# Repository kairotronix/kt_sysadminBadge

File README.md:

# SysAdmin Badge

This is the PCB design for the SysAdmin Day badge.

The badge design is inspired by deep thought, from The Hitchhiker's Guide to the Galaxy.

The LCD being used is a standard 1.3" 240x240 display from Ali Express. Searching `1.3 inch IPS display TFT LCD 1.3" Display Screen Module 240*240 ST7789 Drive IC SPI HD Full Color for IPS Display Module 240X240` and selecting the "welded" or "soldered" variety will yield the correct board. 

The soldered-on cable was chosen for cost reduction.

# What is the idea
In case of fire, a quick reaction is needed, but if you just woke up, if you are in the bathroom or in any compromising situation, the sysadmin must always respond to the user, and then fix the incident.

For this reason, we have designed a random excuse generator that will give you a perfect SLA, even in desperate moments.

Note: Answers may be satirical, so use at your own risk. 

## History
The System Administrator Appreciation Day, It is celebrated on the last Friday of July since the year 2000.

The holiday was started by a system administrator nicknamed Sleeping Beauty (AS). He got his inspiration from a Hewlett-Packard magazine ad, in which an administrator's co-workers gave him flowers and a fruit basket for setting up their new printers and a pillow to rest on in their spare time.

Wait… what exactly is SysAdmin Day? it’s only the single greatest 24 hours on the planet… and pretty much the most important holiday of the year. It’s also the perfect opportunity to pay tribute to the heroic men and women who, come rain or shine, prevent disasters, keep IT secure and put out tech fires left and right.

At this point, you may be thinking, “Great. I get it. My SysAdmin is a rock star. But now what?” Glad you asked! Proper observation of SysAdmin Day includes (but is not limited to):

Cake & Ice cream

Pizza

Cards

Gifts

Words of gratitude

Custom t-shirts celebrating the epic greatness of your SysAdmin

Balloons

Confetti

Did I say gifts

# Conclusion
Why make one badge electronic? Because is one good gift of your SysAdmin.

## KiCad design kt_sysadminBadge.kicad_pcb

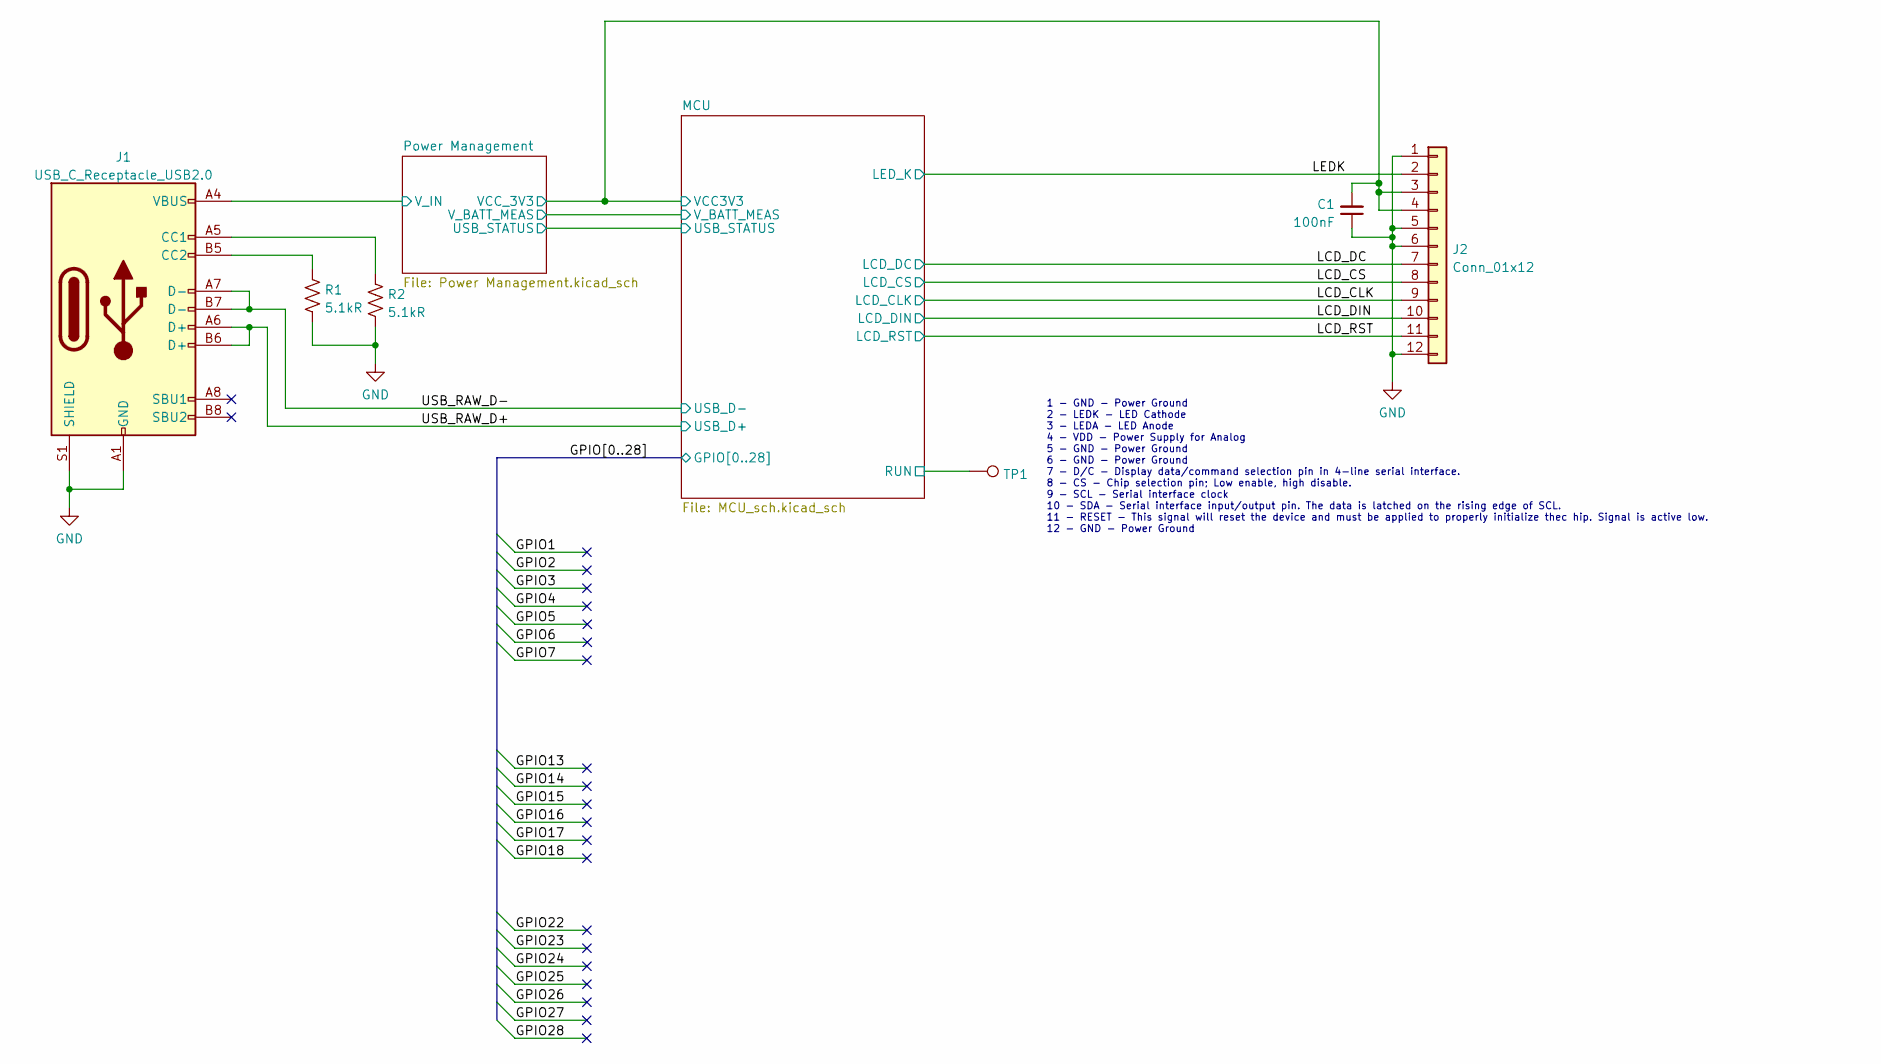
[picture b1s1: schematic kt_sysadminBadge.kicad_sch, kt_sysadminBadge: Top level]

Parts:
C1: 100nF; C_0603_1608Metric_Pad1.08x0.95mm_HandSolder; MFG P/N CL10B104KB8NNNC; LCSC P/N C1591
J1: USB_C_Receptacle_USB2.0; USB_C_Receptacle_XKB_U262-16XN-4BVC11; MFG P/N U262-161N-4BVC11; LCSC P/N C319148
J2: Conn_01x12; st7789-240-240
R1, R2: 5.1kR; R_0603_1608Metric_Pad0.98x0.95mm_HandSolder
TP1: TestPoint; TestPoint_Pad_D1.0mm

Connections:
/LCD_CLK: J2.9; also elsewhere on the board
/LCD_CS: J2.8; also elsewhere on the board
/LCD_DC: J2.7; also elsewhere on the board
/LCD_DIN: J2.10; also elsewhere on the board
/LCD_RST: J2.11; also elsewhere on the board
/LEDK: J2.2; also elsewhere on the board
/MCU/RUN: TP1.1; also elsewhere on the board
/MCU/VCC3V3: C1.2, J2.3, J2.4; also elsewhere on the board
/Power Management/V_USB: J1.A4 (VBUS), J1.A9 (VBUS), J1.B4 (VBUS), J1.B9 (VBUS); also elsewhere on the board
/USB_RAW_D+: J1.A6 (D+), J1.B6 (D+); also elsewhere on the board
/USB_RAW_D-: J1.A7 (D-), J1.B7 (D-); also elsewhere on the board
GND: C1.1, J1.A1 (GND), J1.A12 (GND), J1.B1 (GND), J1.B12 (GND), J1.S1 (SHIELD), J2.1, J2.5, J2.6, J2.12, R1.2, R2.2; also elsewhere on the board
unnamed: J1.A5 (CC1), R2.1
unnamed: J1.B5 (CC2), R1.1

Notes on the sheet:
1 - GND - Power Ground 2 - LEDK - LED Cathode 3 - LEDA - LED Anode 4 - VDD - Power Supply for Analog 5 - GND - Power Ground 6 - GND - Power Ground 7 - D/C - Display data/command selection pin in 4-line serial interface. 8 - CS - Chip selection pin; Low enable, high disable. 9 - SCL - Serial interfa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

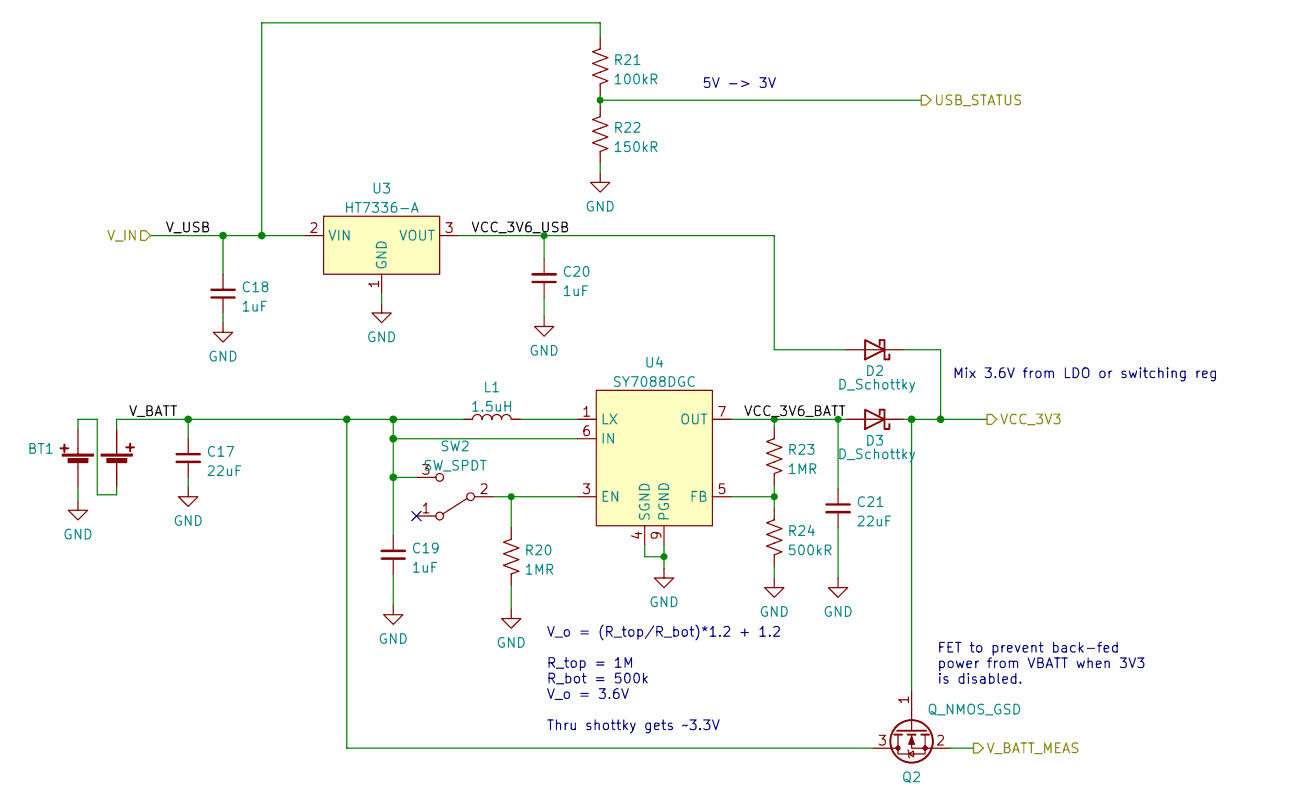
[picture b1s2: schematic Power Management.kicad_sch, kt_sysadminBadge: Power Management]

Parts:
BT1: MFG P/N BH-AAA-B5AA001; LCSC P/N C964881
C17, C21: 22uF; C_0805_2012Metric_Pad1.18x1.45mm_HandSolder; MFG P/N CL21A226MAYNNNE; LCSC P/N C602037
C18, C19, C20: 1uF; C_0603_1608Metric_Pad1.08x0.95mm_HandSolder; MFG P/N CL10A105KO8NNNC; LCSC P/N C1592
D2, D3: D_Schottky; D_SMA_Handsoldering; MFG P/N SS24; LCSC P/N C266555
L1: 1.5uH; L_1008_2520Metric_Pad1.43x2.20mm_HandSolder; MFG P/N HEI252012A-1R5M-Q8; LCSC P/N C285916
Q2: Q_NMOS_GSD; SC-59_Handsoldering; MFG P/N AP2302B; LCSC P/N C406812
R20, R23: 1MR; R_0603_1608Metric_Pad0.98x0.95mm_HandSolder; MFG P/N ARG03BTC1004; LCSC P/N C319876
R21: 100kR; R_0603_1608Metric_Pad0.98x0.95mm_HandSolder; MFG P/N AR03BTCX1003; LCSC P/N C335092
R22: 150kR; R_0603_1608Metric_Pad0.98x0.95mm_HandSolder; MFG P/N AR03BTCX1503; LCSC P/N C319969
R24: 500kR; R_0603_1608Metric_Pad0.98x0.95mm_HandSolder; MFG P/N AR03BTC5003N; LCSC P/N C412382
SW2: SW_SPDT; SW_SPDT_PCM12; MFG P/N K3-1296S-E2; LCSC P/N C136659
U3: HT7336-A; SOT-89-3_Handsoldering; MFG P/N HT7336-A; LCSC P/N C347192
U4: SY7088DGC; DFN-8-1EP_3x2mm_P0.5mm_EP1.7x1.4mm; MFG P/N SY7088DGC; LCSC P/N C178240

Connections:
/MCU/USB_STATUS: R21.2, R22.1; also elsewhere on the board
/MCU/VCC3V3: D2.1 (K), D3.1 (K), Q2.1 (G); also elsewhere on the board
/MCU/V_BATT_MEAS: Q2.2 (S); also elsewhere on the board
/Power Management/VCC_3V6_BATT: C21.1, D3.2 (A), R23.1, U4.7 (OUT), U4.8 (OUT)
/Power Management/VCC_3V6_USB: C20.2, D2.2 (A), U3.3 (VOUT)
/Power Management/V_BATT: BT1.2 (+), C17.1, C19.2, L1.1, Q2.3 (D), SW2.3 (C), U4.6 (IN)
/Power Management/V_USB: C18.2, R21.1, U3.2 (VIN); also elsewhere on the board
GND: BT1.3 (-), C17.2, C18.1, C19.1, C20.1, C21.2, R20.2, R22.2, R24.2, U3.1 (GND), U4.4 (SGND), U4.9 (PGND); also elsewhere on the board
unnamed: BT1.1 (-), BT1.4 (+)
unnamed: L1.2, U4.1 (LX), U4.2 (LX)
unnamed: R20.1, SW2.2 (B), U4.3 (EN)
unnamed: R23.2, R24.1, U4.5 (FB)

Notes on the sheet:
V_o = (R_top/R_bot)*1.2 + 1.2 R_top = 1M R_bot = 500k V_o = 3.6V Thru shottky gets ~3.3V
Mix 3.6V from LDO or switching reg
5V -> 3V
FET to prevent back-fed power from VBATT when 3V3 is disabled.

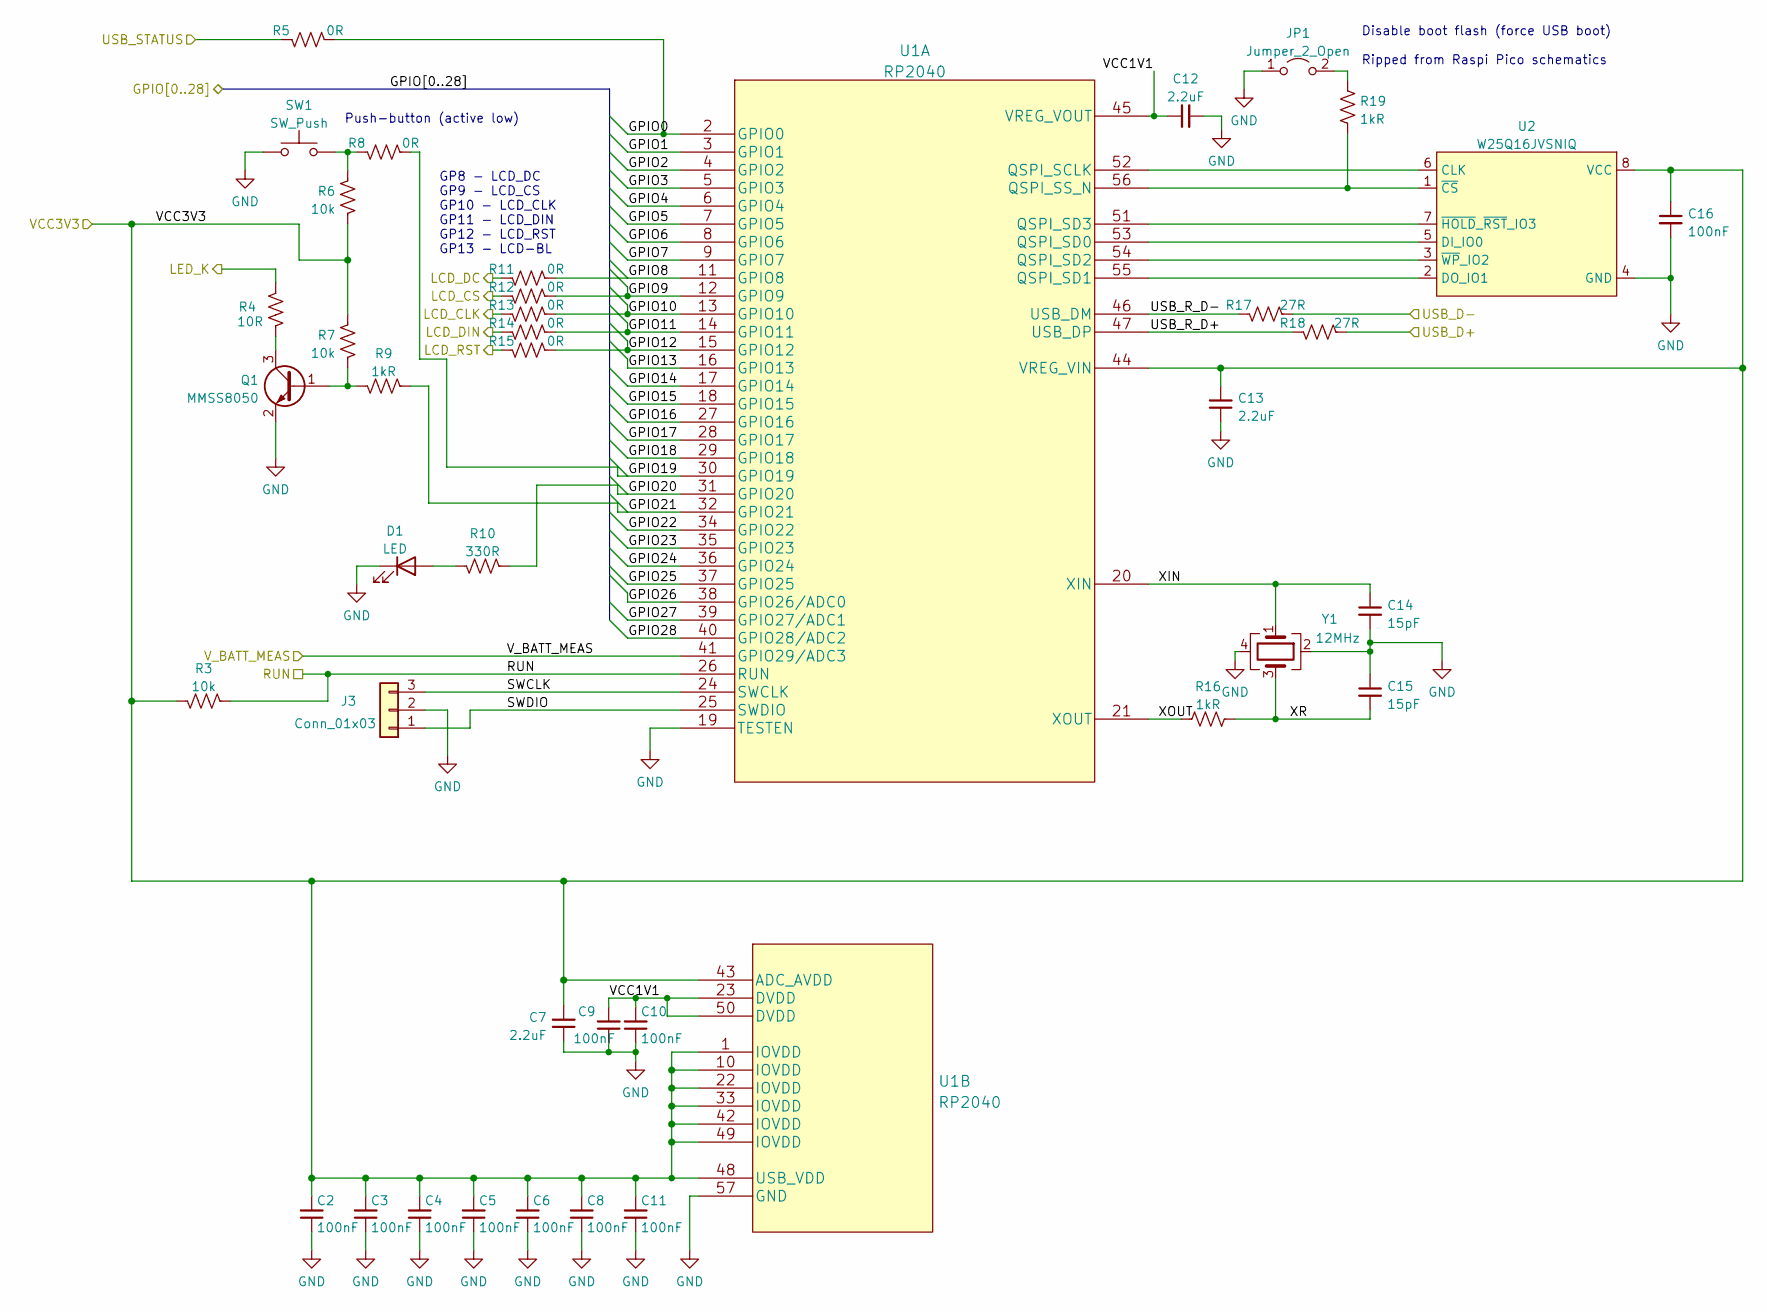
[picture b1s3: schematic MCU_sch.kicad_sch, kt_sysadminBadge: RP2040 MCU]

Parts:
C2, C3, C4, C5, C6, C8, C9, C10, C11, C16: 100nF; C_0603_1608Metric_Pad1.08x0.95mm_HandSolder; MFG P/N CL10B104KB8NNNC; LCSC P/N C1591
C7, C12, C13: 2.2uF; C_0603_1608Metric_Pad1.08x0.95mm_HandSolder; MFG P/N CL10A225KO8NNNC; LCSC P/N C23630
C14, C15: 15pF; C_0603_1608Metric_Pad1.08x0.95mm_HandSolder; MFG P/N CC0603JRNPO9BN150; LCSC P/N C107037
D1: LED; LED_D3.0mm; MFG P/N 204-10SURD/S530-A3-L; LCSC P/N C99771
J3: Conn_01x03; PinHeader_1x03_P2.54mm_Vertical
JP1: Jumper_2_Open; SolderJumper-2_P1.3mm_Open_TrianglePad1.0x1.5mm
Q1: MMSS8050; SC-59_Handsoldering; MFG P/N MMSS8050-H-TP; LCSC P/N C90158
R3, R6, R7: 10k; R_0603_1608Metric_Pad0.98x0.95mm_HandSolder; MFG P/N ARG03BTC1002; LCSC P/N C98220
R4: 10R; R_0603_1608Metric_Pad0.98x0.95mm_HandSolder; MFG P/N ERJUP3J100V; LCSC P/N C309083
R5, R8, R11, R12, R13, R14, R15: 0R; R_0603_1608Metric_Pad0.98x0.95mm_HandSolder; MFG P/N RC0603FR-0710KL; LCSC P/N C491193
R9, R16, R19: 1kR; R_0603_1608Metric_Pad0.98x0.95mm_HandSolder; MFG P/N ERJPB3B1001V; LCSC P/N C193680
R10: 330R; R_0603_1608Metric_Pad0.98x0.95mm_HandSolder; MFG P/N ERJ3RBD3300V; LCSC P/N C416699
R17, R18: 27R; R_0603_1608Metric_Pad0.98x0.95mm_HandSolder; MFG P/N ERJ3GEYJ270V; LCSC P/N C403464
SW1: SW_Push; SW_Push_1P1T_NO_6x6mm_H9.5mm; MFG P/N TSA063G50-250; LCSC P/N C294565
U1: RP2040; IC57_RP2040; MFG P/N RP2040; LCSC P/N C2040
U2: W25Q16JVSNIQ; SOIC-8_3.9x4.9mm_P1.27mm; MFG P/N W25Q16JVSNIQ; LCSC P/N C115407
Y1: 12MHz; Crystal_SMD_3225-4Pin_3.2x2.5mm_HandSoldering; MFG P/N 3TJ412000UYFBC; LCSC P/N C2681245

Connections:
/GPIO0: R5.1, U1.2 (GPIO0); also elsewhere on the board
/GPIO8: R11.1, U1.11 (GPIO8); also elsewhere on the board
/GPIO9: R12.1, U1.12 (GPIO9); also elsewhere on the board
/GPIO10: R13.1, U1.13 (GPIO10); also elsewhere on the board
/GPIO11: R14.1, U1.14 (GPIO11); also elsewhere on the board
/GPIO12: R15.1, U1.15 (GPIO12); also elsewhere on the board
/GPIO19: R8.1, U1.30 (GPIO19); also elsewhere on the board
/GPIO20: R10.1, U1.31 (GPIO20); also elsewhere on the board
/GPIO21: R9.1, U1.32 (GPIO21); also elsewhere on the board
/LCD_CLK: R13.2; also elsewhere on the board
/LCD_CS: R12.2; also elsewhere on the board
/LCD_DC: R11.2; also elsewhere on the board
/LCD_DIN: R14.2; also elsewhere on the board
/LCD_RST: R15.2; also elsewhere on the board
/LEDK: R4.1; also elsewhere on the board
/MCU/RUN: R3.2, U1.26 (RUN); also elsewhere on the board
/MCU/SWCLK: J3.3, U1.24 (SWCLK); also elsewhere on the board
/MCU/SWDIO: J3.1, U1.25 (SWDIO); also elsewhere on the board
/MCU/USB_R_D+: R18.2, U1.47 (USB_DP); also elsewhere on the board
/MCU/USB_R_D-: R17.2, U1.46 (USB_DM); also elsewhere on the board
/MCU/USB_STATUS: R5.2; also elsewhere on the board
/MCU/VCC1V1: C9.2, C10.2, C12.1, U1.23 (DVDD), U1.45 (VREG_VOUT), U1.50 (DVDD); also elsewhere on the board
/MCU/VCC3V3: C2.2, C3.2, C4.2, C5.2, C6.2, C7.2, C8.2, C11.2, C13.2, C16.1, R3.1, R6.2, R7.1, U1.1 (IOVDD), U1.10 (IOVDD), U1.22 (IOVDD), U1.33 (IOVDD), U1.42 (IOVDD), U1.43 (ADC_AVDD), U1.44 (VREG_VIN), U1.48 (USB_VDD), U1.49 (IOVDD), U2.8 (VCC); also elsewhere on the board
/MCU/XIN: C14.1, U1.20 (XIN), Y1.1; also elsewhere on the board
/MCU/XOUT: R16.2, U1.21 (XOUT); also elsewhere on the board
/MCU/XR: C15.2, R16.1, Y1.3
/USB_RAW_D+: R18.1; also elsewhere on the board
/USB_RAW_D-: R17.1; also elsewhere on the board
GND: C2.1, C3.1, C4.1, C5.1, C6.1, C7.1, C8.1, C9.1, C10.1, C11.1, C12.2, C13.1, C14.2, C15.1, C16.2, D1.1 (K), J3.2, JP1.1 (A), Q1.2 (E), SW1.2, U1.19 (TESTEN), U1.57 (GND), U2.4 (GND), Y1.2, Y1.4; also elsewhere on the board
unnamed: D1.2 (A), R10.2
unnamed: JP1.2 (B), R19.1
unnamed: Q1.1 (B), R7.2, R9.2
unnamed: Q1.3 (C), R4.2
unnamed: R6.1, R8.2, SW1.1
unnamed 63: R19.2, U1.56 (QSPI_SS_N), U2.1 (~CS); also elsewhere on the board
unnamed 66: U1.51 (QSPI_SD3), U2.7 (~HOLD_~RST_IO3); also elsewhere on the board
unnamed 67: U1.52 (QSPI_SCLK), U2.6 (CLK); also elsewhere on the board
unnamed 68: U1.53 (QSPI_SD0), U2.5 (DI_IO0); also elsewhere on the board
unnamed 69: U1.54 (QSPI_SD2), U2.3 (~WP_IO2); also elsewhere on the board
unnamed 70: U1.55 (QSPI_SD1), U2.2 (DO_IO1); also elsewhere on the board

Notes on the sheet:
Disable boot flash (force USB boot) Ripped from Raspi Pico schematics
Push-button (active low)
GP8 - LCD_DC GP9 - LCD_CS GP10 - LCD_CLK GP11 - LCD_DIN GP12 - LCD_RST GP13 - LCD-BL

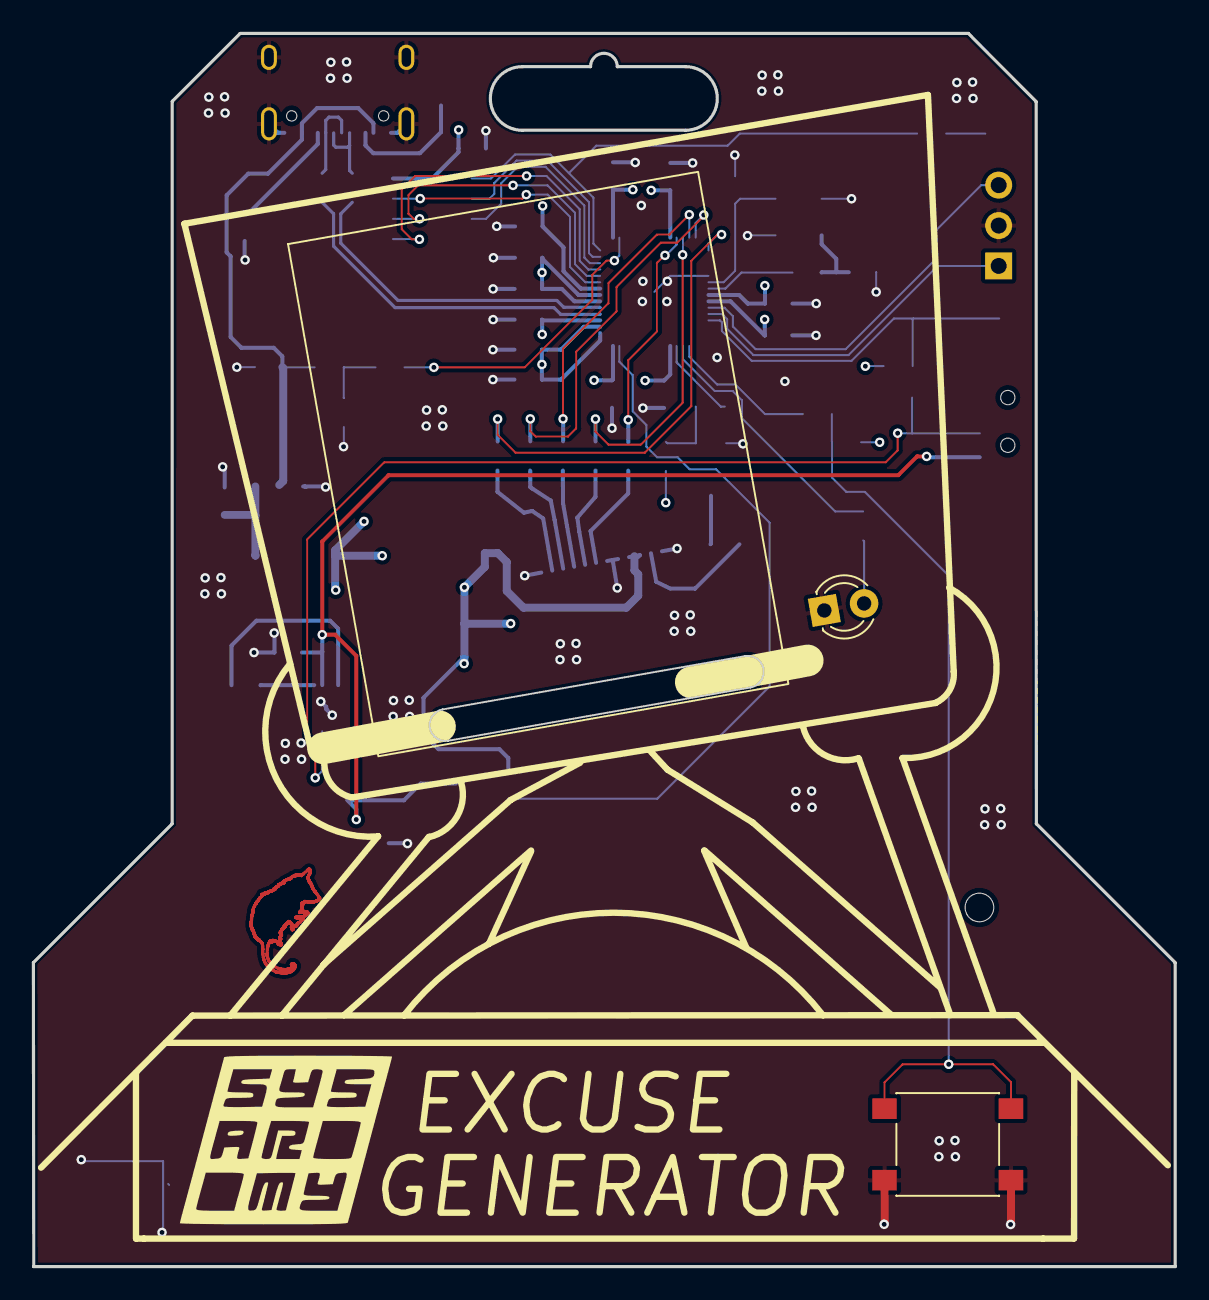
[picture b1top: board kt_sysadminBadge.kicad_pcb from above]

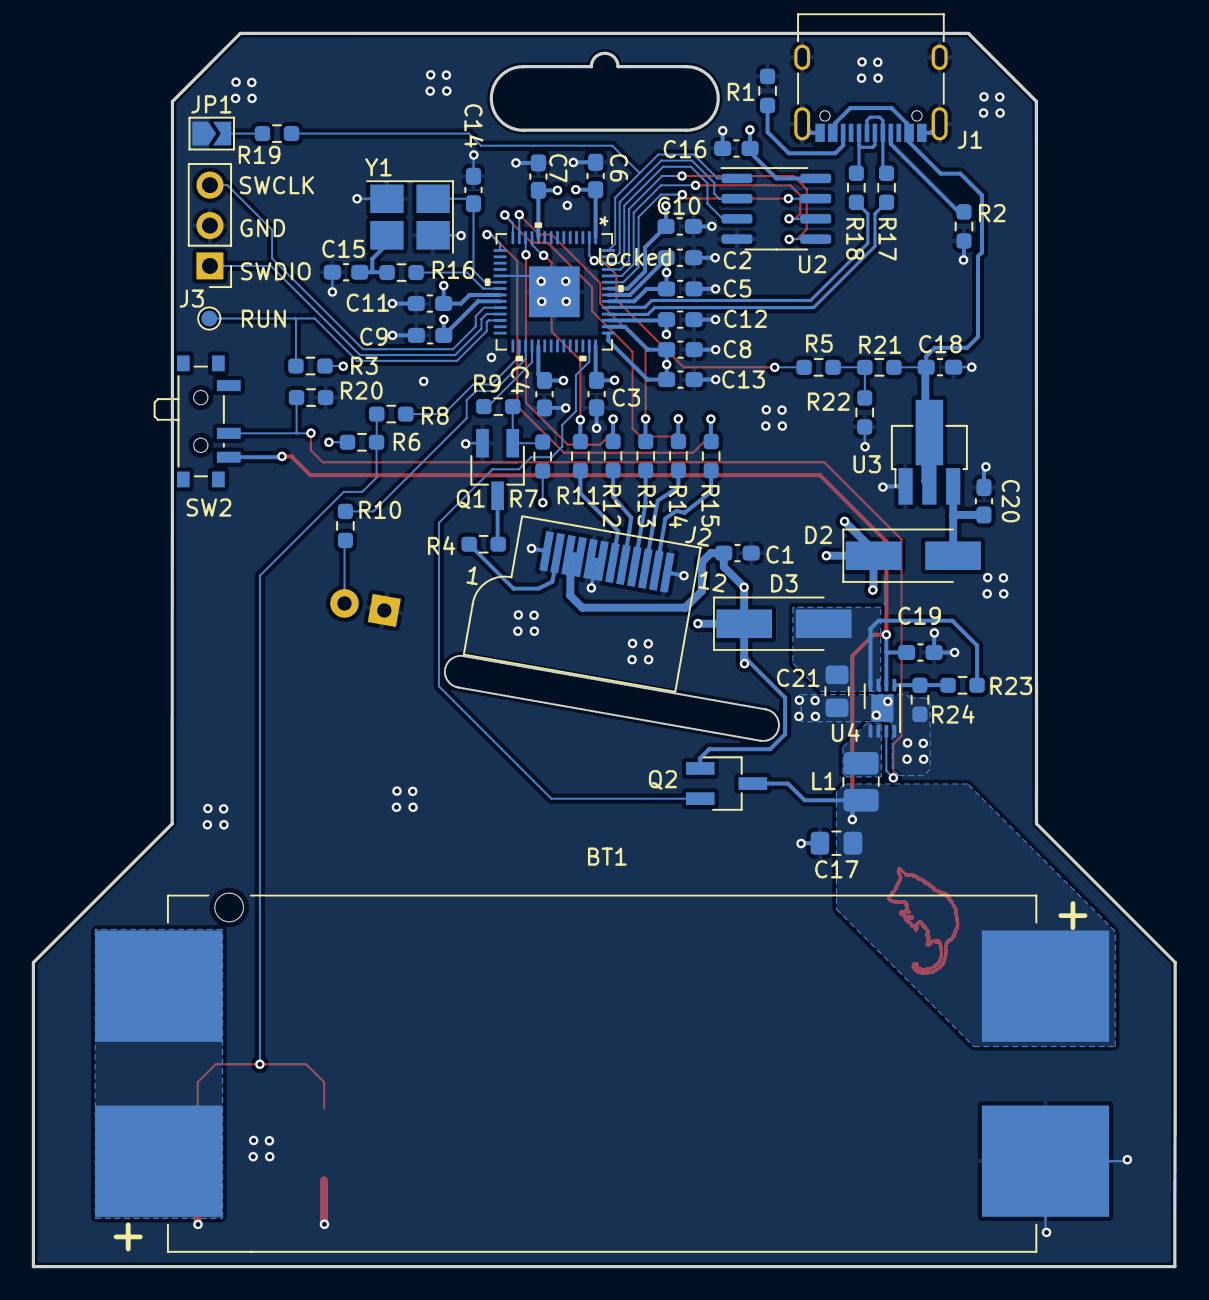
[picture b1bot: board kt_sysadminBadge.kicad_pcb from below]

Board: 4 copper layers, 71.8 x 77.5 mm, 64 parts (61 on the bottom side), 51 nets.

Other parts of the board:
locked: locked; IC57_RP2040

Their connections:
/GPIO0: locked.2 (GPIO0); also elsewhere on the board
/GPIO8: locked.11 (GPIO8); also elsewhere on the board
/GPIO9: locked.12 (GPIO9); also elsewhere on the board
/GPIO10: locked.13 (GPIO10); also elsewhere on the board
/GPIO11: locked.14 (GPIO11); also elsewhere on the board
/GPIO12: locked.15 (GPIO12); also elsewhere on the board
/GPIO19: locked.30 (GPIO19); also elsewhere on the board
/GPIO20: locked.31 (GPIO20); also elsewhere on the board
/GPIO21: locked.32 (GPIO21); also elsewhere on the board
/MCU/RUN: locked.26 (RUN); also elsewhere on the board
/MCU/SWCLK: locked.24 (SWCLK); also elsewhere on the board
/MCU/SWDIO: locked.25 (SWDIO); also elsewhere on the board
/MCU/USB_R_D+: locked.47 (USB_DP); also elsewhere on the board
/MCU/USB_R_D-: locked.46 (USB_DM); also elsewhere on the board
/MCU/VCC1V1: locked.23 (DVDD), locked.45 (VREG_VOUT), locked.50 (DVDD); also elsewhere on the board
/MCU/VCC3V3: locked.1 (IOVDD), locked.10 (IOVDD), locked.22 (IOVDD), locked.33 (IOVDD), locked.42 (IOVDD), locked.43 (ADC_AVDD), locked.44 (VREG_VIN), locked.48 (USB_VDD), locked.49 (IOVDD); also elsewhere on the board
/MCU/V_BATT_MEAS: locked.41 (GPIO29/ADC3); also elsewhere on the board
/MCU/XIN: locked.20 (XIN); also elsewhere on the board
/MCU/XOUT: locked.21 (XOUT); also elsewhere on the board
GND: locked.19 (TESTEN), locked.57 (GND); also elsewhere on the board
unnamed 63: locked.56 (QSPI_SS_N); also elsewhere on the board
unnamed 66: locked.51 (QSPI_SD3); also elsewhere on the board
unnamed 67: locked.52 (QSPI_SCLK); also elsewhere on the board
unnamed 68: locked.53 (QSPI_SD0); also elsewhere on the board
unnamed 69: locked.54 (QSPI_SD2); also elsewhere on the board
unnamed 70: locked.55 (QSPI_SD1); also elsewhere on the board

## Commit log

2022-05-03 Addming main files
2022-05-20 Modified resistor value and changed battery holder.
2022-05-20 reverting to old battery holder (known good)
2022-05-20 Modifying footprint in sub-schematic page
2022-05-21 Updating design, adding reverse polarity protection
2022-10-07 Add new Readme
2022-10-07 add ci
2022-10-07 add badge of state CI
2022-10-07 change path of files
2022-10-07 change order of files
2022-10-07 change version to actions upload, and path of output
2022-10-07 change version to actions checkout

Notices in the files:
parts and their libraries:
Copyright 2021 Accelerated Designs. All rights reserved.
